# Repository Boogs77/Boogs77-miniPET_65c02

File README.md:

# Boogs77-miniPET: 65C02-Based Retro Computer

The **Boogs77-miniPET** is a compact, high-performance 8-bit computer inspired by the iconic Commodore PET aesthetics. Built around the **W65C02S** processor, this project utilizes the modular architecture of the [BO6502 System](https://github.com/Boogs77/BO6502_65C02-based_modular_computer) and integrates it into a custom-designed, 3D-printed enclosure.

---

## 🧠 System Architecture & Modules

The internal logic of the miniPET is derived directly from the modular boards of the BO6502 project. Each core component follows the same electrical and logical specifications:

### ⚙️ Core Processing Unit (CPU, RAM, ROM)
The system's "brain" and memory management are based on the high-reliability design of the BO6502:
* **CPU:** Western Design Center **W65C02S**, allowing for modern high-speed operation while maintaining full 6502 compatibility. Reference: [BO6502 CPU](https://github.com/Boogs77/BO6502_65C02-based_modular_computer/tree/main/BO6502%20CPU).
* **Clock:** System operates with a stable **1MHz** clock frequency. Reference: [BO6502 CPU](https://github.com/Boogs77/BO6502_65C02-based_modular_computer/tree/main/BO6502%20CPU).

### 🗺️ Memory Map
The memory layout is organized to ensure compatibility with the system firmware and modular hardware:
* **RAM (32KB):** Mapped from **$0000** to **$7FFF**. Reference: [BO6502 RAM](https://github.com/Boogs77/BO6502_65C02-based_modular_computer/tree/main/BO6502%20RAM).
* **ROM (32KB):** Mapped from **$8000** to **$FFFF**. Reference: [BO6502 ROM](https://github.com/Boogs77/BO6502_65C02-based_modular_computer/tree/main/BO6502%20ROM).

### 📟 Display Interface (BIGLCD)
The visual output is handled by the **BIGLCD** module. 
* **Addressing:** The module is mapped and accessible at memory address **$D19X**.
* **Reference:** [BO6502 BIGLCD](https://github.com/Boogs77/BO6502_65C02-based_modular_computer/tree/main/BO6502%20BIGLCD).

### ⌨️ Keyboard Input
Input is managed via a dedicated matrix keyboard interface.
* **Addressing:** The keyboard is mapped and accessible at memory address **$D18X**.
* **Reference:** [BO6502 KeyBoard Module](https://github.com/Boogs77/BO6502_65C02-based_modular_computer/tree/main/BO6502%20KEYb).

### 🔌 Serial Communication
Asynchronous communication is provided for external terminal access.
* **Addressing:** Accessible at the **$CXXX** memory range.
* **Reference:** [BO6502 Serial Module](https://github.com/Boogs77/BO6502_65C02-based_modular_computer/tree/main/BO6502%20SERIAL).

---

## 💻 Software & Firmware

The Boogs77-miniPET features a classic software environment for 6502 enthusiasts:
* **System Monitor:** The computer implements the legendary **Wozmon** monitor, providing a low-level interface for memory inspection and machine code execution.
* **Microsoft BASIC:** The firmware includes **MS BASIC**, allowing for high-level programming.
* **Execution:** BASIC can be launched directly from the monitor by executing from location **$8000**.

---

## 🏗️ Enclosure & 3D Design

One of the most distinctive features of this project is its custom case, modified using **Autodesk Fusion 360** from the original design at [commodorepetmini.com](https://commodorepetmini.com/). The case was printed on an **Anycubic Kobra S1**.

---

## 📋 Bill of Materials (BOM)

| Component | Description | Quantity |
| :--- | :--- | :--- |
| **W65C02S** | CMOS 8-bit Microprocessor | 1 |
| **AS6C62256** | 32K x 8 Static RAM | 1 |
| **AT28C256** | 32K x 8 EEPROM | 1 |
| **W65C22 (VIA)** | Versatile Interface Adapter | 2 |
| **NE555** | Precision Timer (Reset Circuit) | 1 |
| **BIGLCD** | High Contrast LCD Module | 1 |

👉 **[View Full BOM for Components](https://github.com/Boogs77/Boogs77-miniPET_65c02/blob/main/export/miniPET_bom.md)**

---

## 🔗 Useful Links & Resources

To replicate this build, you can refer to the following hardware files:

* **Eagle Design Files:** [Project PCB Schematics & Layouts](https://github.com/Boogs77/Boogs77-miniPET_65c02/tree/main/eagle)
* **CPU Module:** [BO6502 CPU Reference](https://github.com/Boogs77/BO6502_65C02-based_modular_computer/tree/main/BO6502%20CPU)
* **ROM Module:** [BO6502 ROM Reference](https://github.com/Boogs77/BO6502_65C02-based_modular_computer/tree/main/BO6502%20ROM)
* **RAM Module:** [BO6502 RAM Reference](https://github.com/Boogs77/BO6502_65C02-based_modular_computer/tree/main/BO6502%20RAM)
* **Serial Module:** [BO6502 Serial Reference](https://github.com/Boogs77/BO6502_65C02-based_modular_computer/tree/main/BO6502%20SERIAL)
* **Keyboard Module:** [BO6502 KeyBoard Reference](https://github.com/Boogs77/BO6502_65C02-based_modular_computer/tree/main/BO6502%20KEYb)
* **Display Module:** [BO6502 BIGLCD Reference](https://github.com/Boogs77/BO6502_65C02-based_modular_computer/tree/main/BO6502%20BIGLCD)

---

## 🖼️ Project Gallery

Internal assembly and detailed realization stages:

---
*Created by Boogs77 - 2026*

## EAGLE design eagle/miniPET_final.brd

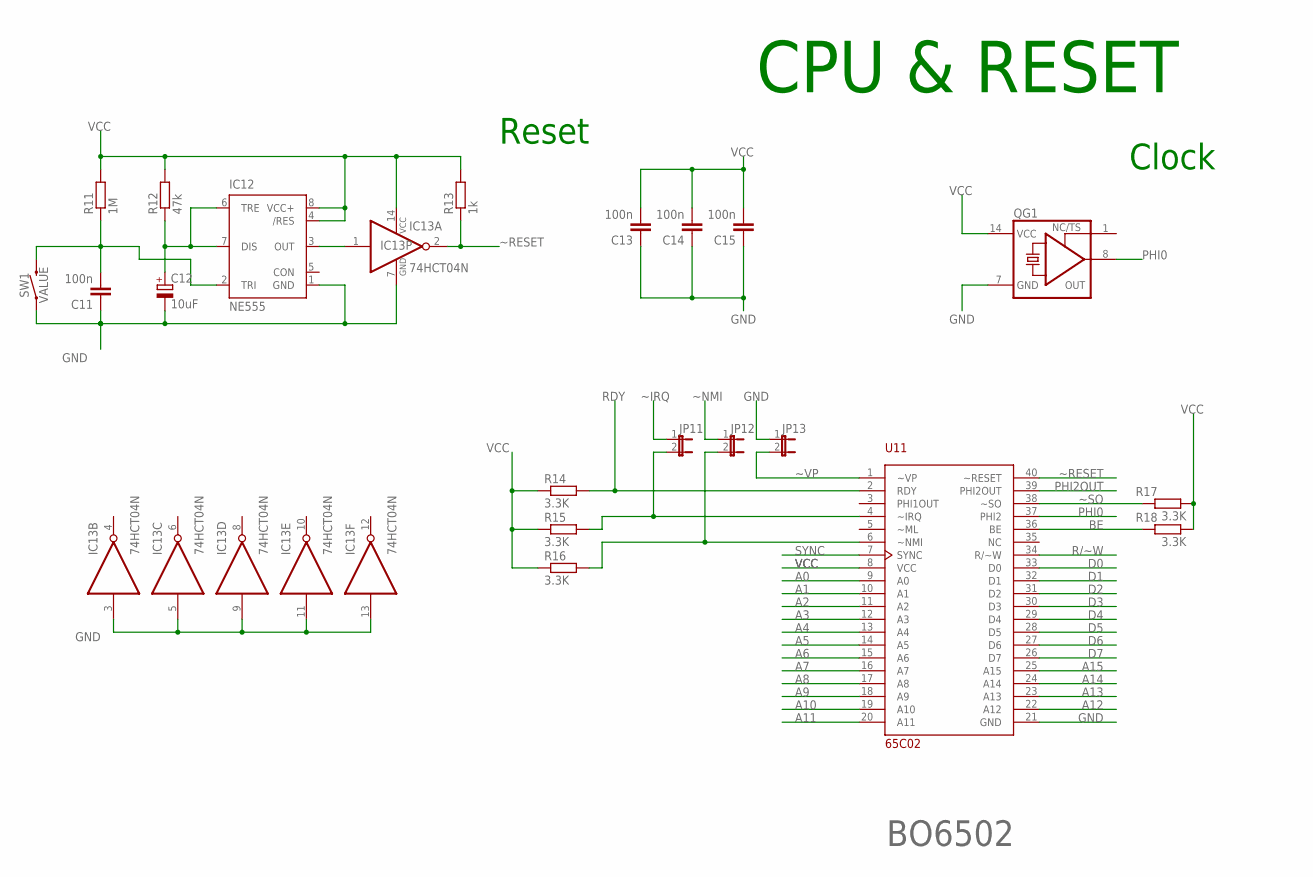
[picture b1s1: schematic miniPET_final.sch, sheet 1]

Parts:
C11, C13, C14, C15: 100n; C025-025X050
C12: 10uF; B45181A
IC12: NE555; DIL-08
IC13: 74HCT04N; DIL14
JP11, JP12, JP13: JP1E; JP1
QG1: XO-14; DIL14S
R11: 1M; 0207/10
R12: 47k; 0207/10
R13: 1k; 0207/10
R14, R15, R16, R17, R18: 3.3K; 0207/10
SW1: MOMENTARY-SWITCH-SPST-PTH-RIGHT-ANGLE-8-020; TACTILE_SWITCH_PTH_RA_8-020
U11: 65C02; DIL40

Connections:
A0: U11.9 (A0); also elsewhere on the board
A1: U11.10 (A1); also elsewhere on the board
A2: U11.11 (A2); also elsewhere on the board
A3: U11.12 (A3); also elsewhere on the board
A4: U11.13 (A4); also elsewhere on the board
A5: U11.14 (A5); also elsewhere on the board
A6: U11.15 (A6); also elsewhere on the board
A7: U11.16 (A7); also elsewhere on the board
A8: U11.17 (A8); also elsewhere on the board
A9: U11.18 (A9); also elsewhere on the board
A10: U11.19 (A10); also elsewhere on the board
A11: U11.20 (A11); also elsewhere on the board
A12: U11.22 (A12); also elsewhere on the board
A13: U11.23 (A13); also elsewhere on the board
A14: U11.24 (A14); also elsewhere on the board
A15: U11.25 (A15); also elsewhere on the board
BE: R18.1, U11.36 (BE)
D0: U11.33 (D0); also elsewhere on the board
D1: U11.32 (D1); also elsewhere on the board
D2: U11.31 (D2); also elsewhere on the board
D3: U11.30 (D3); also elsewhere on the board
D4: U11.29 (D4); also elsewhere on the board
D5: U11.28 (D5); also elsewhere on the board
D6: U11.27 (D6); also elsewhere on the board
D7: U11.26 (D7); also elsewhere on the board
GND: C11.1, C12.-, C13.1, C14.1, C15.1, IC12.1 (GND), IC13.3 (I), IC13.5 (I), IC13.7 (GND), IC13.9 (I), IC13.11 (I), IC13.13 (I), JP13.1, QG1.7 (GND), SW1.1, U11.21 (GND); also elsewhere on the board
unnamed: JP11.2, R15.2, U11.4 (~IRQ)
unnamed: JP12.2, R16.2, U11.6 (~NMI)
unnamed: C12.+, IC12.6 (TRE), IC12.7 (DIS), R12.1
unnamed: C11.2, IC12.2 (TRI), R11.1, SW1.2
unnamed: IC12.3 (OUT), IC13.1 (I)
PHI0: QG1.8 (OUT), U11.37 (PHI2); also elsewhere on the board
PHI2OUT: U11.39 (PHI2OUT)
R/~W: U11.34 (R/~W); also elsewhere on the board
RDY: R14.2, U11.2 (RDY)
SYNC: U11.7 (SYNC)
VCC: C13.2, C14.2, C15.2, IC12.4 (/RES), IC12.8 (VCC+), IC13.14 (VCC), QG1.14 (VCC), R11.2, R12.2, R13.2, R14.1, R15.1, R16.1, R17.2, R18.2, U11.8 (VCC); also elsewhere on the board
~IRQ: JP11.1; also elsewhere on the board
~NMI: JP12.1
~RESET: IC13.2 (O), R13.1, U11.40 (~RESET); also elsewhere on the board
~SO: R17.1, U11.38 (~SO)
~VP: JP13.2, U11.1 (~VP)

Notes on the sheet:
BO6502
CPU & RESET
Clock
Reset

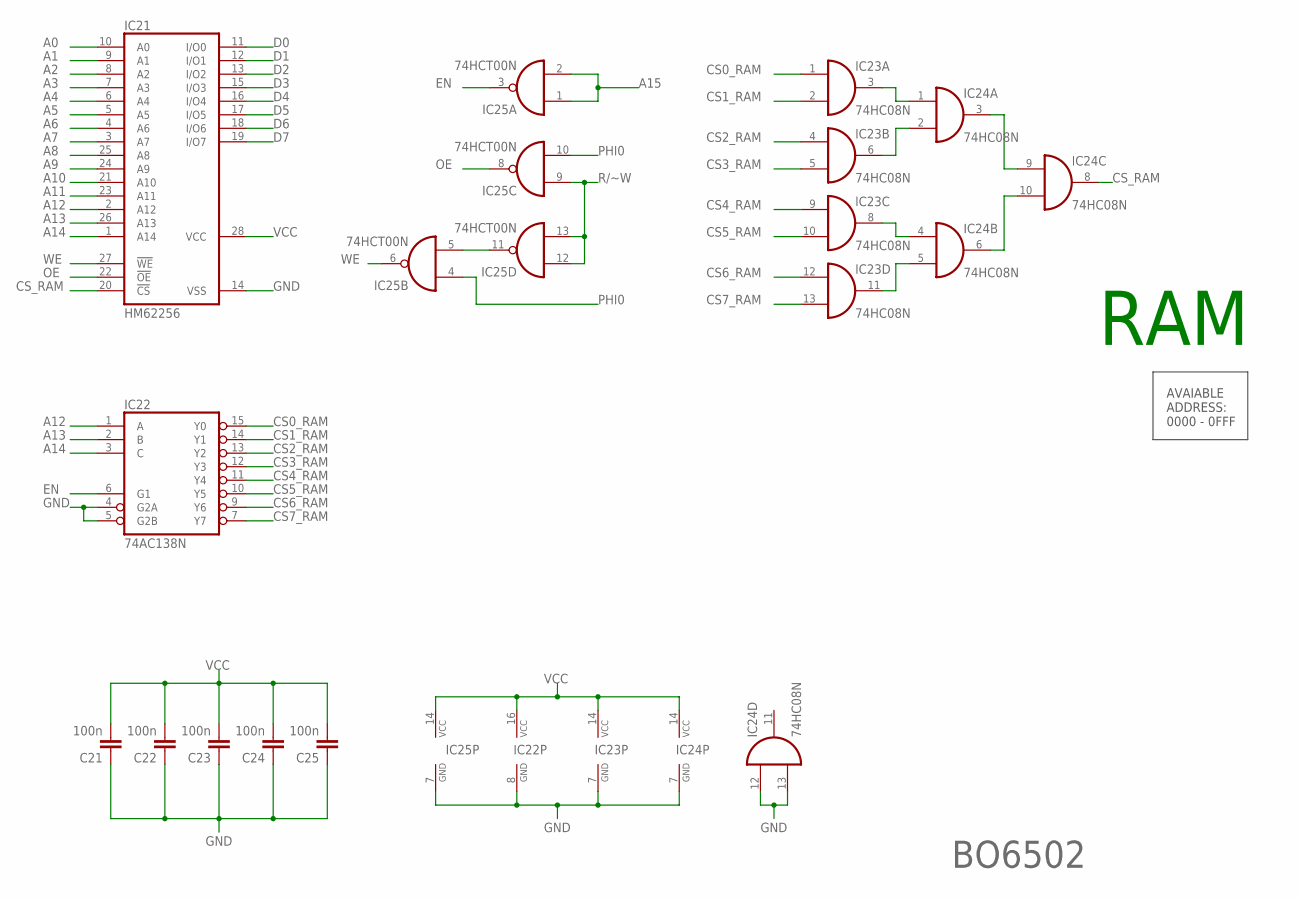
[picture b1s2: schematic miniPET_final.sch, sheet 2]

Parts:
C21, C22, C23, C24, C25: 100n; C025-025X050
IC21: HM62256; DIL28-6
IC22: 74AC138N; DIL16
IC23, IC24: 74HC08N; DIL14
IC25: 74HCT00N; DIL14

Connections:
A0: IC21.10 (A0); also elsewhere on the board
A1: IC21.9 (A1); also elsewhere on the board
A2: IC21.8 (A2); also elsewhere on the board
A3: IC21.7 (A3); also elsewhere on the board
A4: IC21.6 (A4); also elsewhere on the board
A5: IC21.5 (A5); also elsewhere on the board
A6: IC21.4 (A6); also elsewhere on the board
A7: IC21.3 (A7); also elsewhere on the board
A8: IC21.25 (A8); also elsewhere on the board
A9: IC21.24 (A9); also elsewhere on the board
A10: IC21.21 (A10); also elsewhere on the board
A11: IC21.23 (A11); also elsewhere on the board
A12: IC21.2 (A12), IC22.1 (A); also elsewhere on the board
A13: IC21.26 (A13), IC22.2 (B); also elsewhere on the board
A14: IC21.1 (A14), IC22.3 (C); also elsewhere on the board
A15: IC25.1 (I0), IC25.2 (I1); also elsewhere on the board
CS0_RAM: IC22.15 (Y0), IC23.1 (I0)
CS1_RAM: IC22.14 (Y1), IC23.2 (I1)
CS2_RAM: IC22.13 (Y2), IC23.4 (I0)
CS3_RAM: IC22.12 (Y3), IC23.5 (I1)
CS4_RAM: IC22.11 (Y4), IC23.9 (I0)
CS5_RAM: IC22.10 (Y5), IC23.10 (I1)
CS6_RAM: IC22.9 (Y6), IC23.12 (I0)
CS7_RAM: IC22.7 (Y7), IC23.13 (I1)
CS_RAM: IC21.20 (!CS), IC24.8 (O)
D0: IC21.11 (I/O0); also elsewhere on the board
D1: IC21.12 (I/O1); also elsewhere on the board
D2: IC21.13 (I/O2); also elsewhere on the board
D3: IC21.15 (I/O3); also elsewhere on the board
D4: IC21.16 (I/O4); also elsewhere on the board
D5: IC21.17 (I/O5); also elsewhere on the board
D6: IC21.18 (I/O6); also elsewhere on the board
D7: IC21.19 (I/O7); also elsewhere on the board
EN: IC22.6 (G1), IC25.3 (O)
GND: C21.1, C22.1, C23.1, C24.1, C25.1, IC21.14 (VSS), IC22.4 (G2A), IC22.5 (G2B), IC22.8 (GND), IC23.7 (GND), IC24.7 (GND), IC24.12 (I0), IC24.13 (I1), IC25.7 (GND); also elsewhere on the board
unnamed: IC25.5 (I1), IC25.11 (O)
unnamed: IC23.3 (O), IC24.1 (I0)
unnamed: IC23.6 (O), IC24.2 (I1)
unnamed: IC23.8 (O), IC24.4 (I0)
unnamed: IC23.11 (O), IC24.5 (I1)
unnamed: IC24.3 (O), IC24.9 (I0)
unnamed: IC24.6 (O), IC24.10 (I1)
OE: IC21.22 (!OE), IC25.8 (O)
PHI0: IC25.4 (I0), IC25.10 (I1); also elsewhere on the board
R/~W: IC25.9 (I0), IC25.12 (I0), IC25.13 (I1); also elsewhere on the board
VCC: C21.2, C22.2, C23.2, C24.2, C25.2, IC21.28 (VCC), IC22.16 (VCC), IC23.14 (VCC), IC24.14 (VCC), IC25.14 (VCC); also elsewhere on the board
WE: IC21.27 (!WE), IC25.6 (O)

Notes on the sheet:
RAM
BO6502
AVAIABLE ADDRESS: 0000 - 0FFF

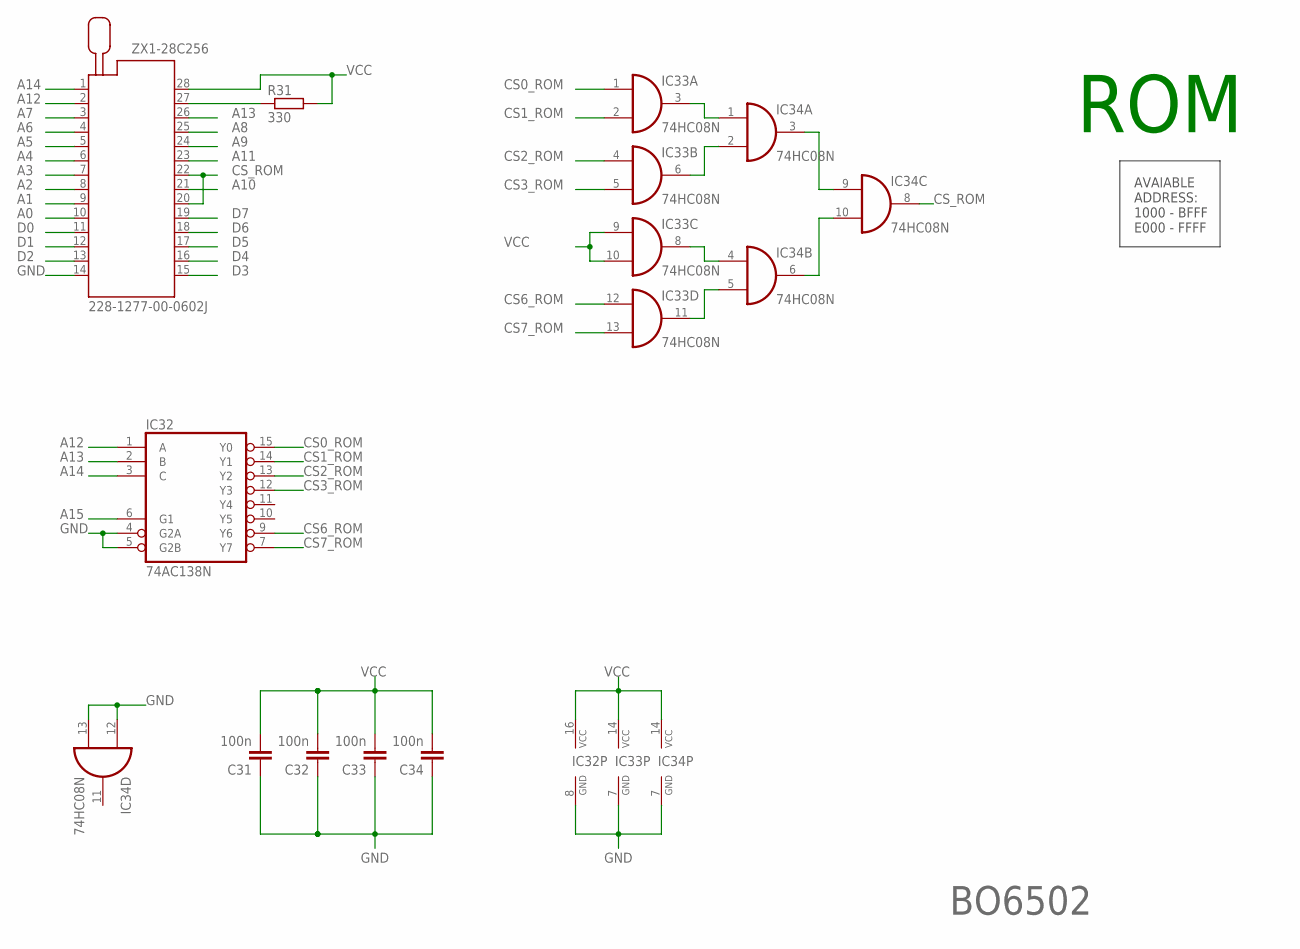
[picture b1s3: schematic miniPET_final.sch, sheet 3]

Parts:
C31, C32, C33, C34: 100n; C025-025X050
IC32: 74AC138N; DIL16
IC33, IC34: 74HC08N; DIL14
R31: 330; 0207/10
ZX1-28C256: 228-1277-00-0602J

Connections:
A0: ZX1-28C256.10; also elsewhere on the board
A1: ZX1-28C256.9; also elsewhere on the board
A2: ZX1-28C256.8; also elsewhere on the board
A3: ZX1-28C256.7; also elsewhere on the board
A4: ZX1-28C256.6; also elsewhere on the board
A5: ZX1-28C256.5; also elsewhere on the board
A6: ZX1-28C256.4; also elsewhere on the board
A7: ZX1-28C256.3; also elsewhere on the board
A8: ZX1-28C256.25; also elsewhere on the board
A9: ZX1-28C256.24; also elsewhere on the board
A10: ZX1-28C256.21; also elsewhere on the board
A11: ZX1-28C256.23; also elsewhere on the board
A12: IC32.1 (A), ZX1-28C256.2; also elsewhere on the board
A13: IC32.2 (B), ZX1-28C256.26; also elsewhere on the board
A14: IC32.3 (C), ZX1-28C256.1; also elsewhere on the board
A15: IC32.6 (G1); also elsewhere on the board
CS0_ROM: IC32.15 (Y0), IC33.1 (I0)
CS1_ROM: IC32.14 (Y1), IC33.2 (I1)
CS2_ROM: IC32.13 (Y2), IC33.4 (I0)
CS3_ROM: IC32.12 (Y3), IC33.5 (I1)
CS6_ROM: IC32.9 (Y6), IC33.12 (I0)
CS7_ROM: IC32.7 (Y7), IC33.13 (I1)
CS_ROM: IC34.8 (O), ZX1-28C256.20, ZX1-28C256.22
D0: ZX1-28C256.11; also elsewhere on the board
D1: ZX1-28C256.12; also elsewhere on the board
D2: ZX1-28C256.13; also elsewhere on the board
D3: ZX1-28C256.15; also elsewhere on the board
D4: ZX1-28C256.16; also elsewhere on the board
D5: ZX1-28C256.17; also elsewhere on the board
D6: ZX1-28C256.18; also elsewhere on the board
D7: ZX1-28C256.19; also elsewhere on the board
GND: C31.1, C32.1, C33.1, C34.1, IC32.4 (G2A), IC32.5 (G2B), IC32.8 (GND), IC33.7 (GND), IC34.7 (GND), IC34.12 (I0), IC34.13 (I1), ZX1-28C256.14; also elsewhere on the board
unnamed: R31.1, ZX1-28C256.27
unnamed: IC33.3 (O), IC34.1 (I0)
unnamed: IC33.6 (O), IC34.2 (I1)
unnamed: IC33.8 (O), IC34.4 (I0)
unnamed: IC33.11 (O), IC34.5 (I1)
unnamed: IC34.3 (O), IC34.9 (I0)
unnamed: IC34.6 (O), IC34.10 (I1)
VCC: C31.2, C32.2, C33.2, C34.2, IC32.16 (VCC), IC33.9 (I0), IC33.10 (I1), IC33.14 (VCC), IC34.14 (VCC), R31.2, ZX1-28C256.28; also elsewhere on the board

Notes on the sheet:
ROM
BO6502
AVAIABLE ADDRESS: 1000 - BFFF E000 - FFFF

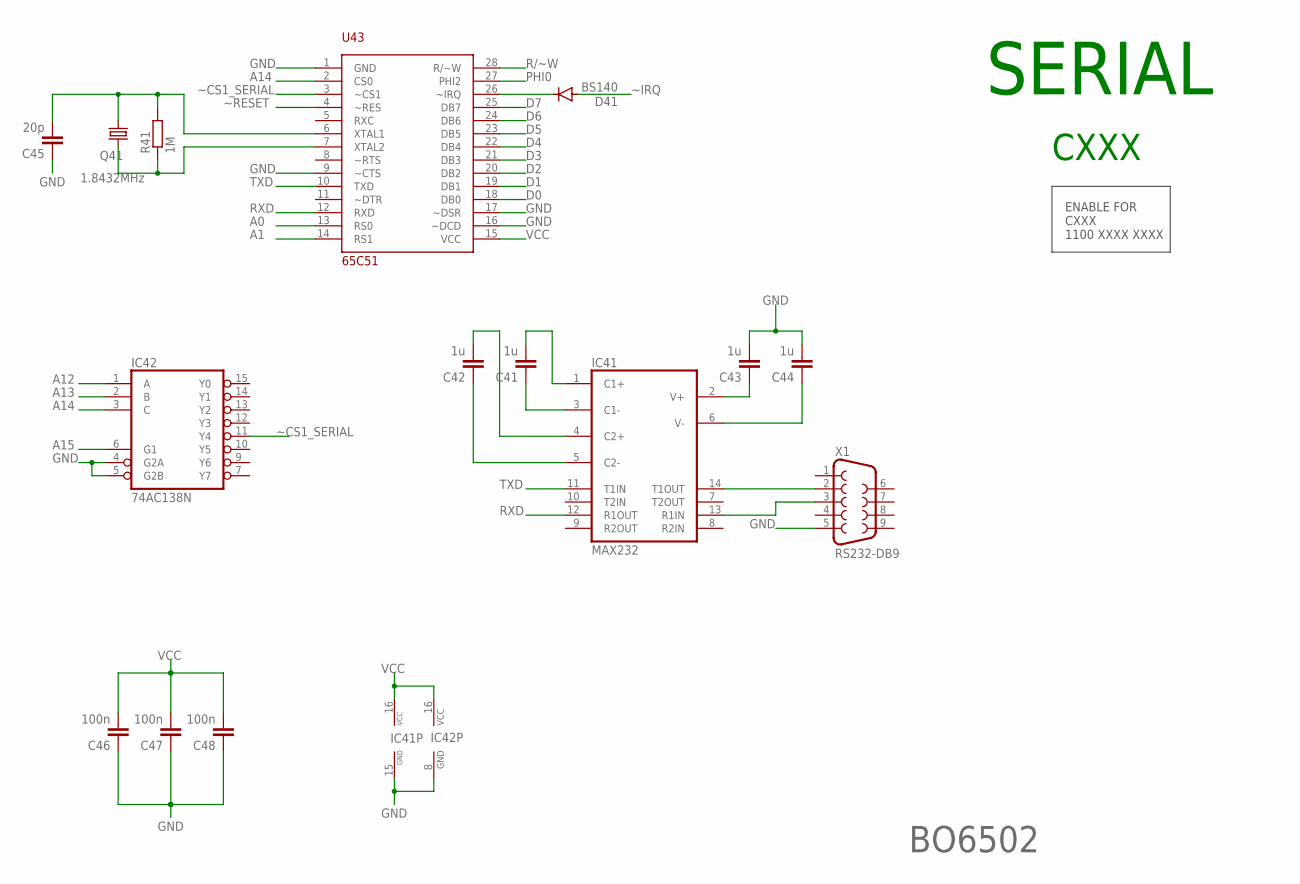
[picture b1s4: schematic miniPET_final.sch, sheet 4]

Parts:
C41, C42, C43, C44: 1u; C050-025X075
C45: 20p; C025-025X050
C46, C47, C48: 100n; C025-025X050
D41: BS140; DO41-10
IC41: MAX232; DIL16
IC42: 74AC138N; DIL16
Q41: 1.8432MHz; HC49/S
R41: 1M; 0207/10
U43: 65C51; DIL28
X1: RS232-DB9; F09HP

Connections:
A0: U43.13 (RS0); also elsewhere on the board
A1: U43.14 (RS1); also elsewhere on the board
A12: IC42.1 (A); also elsewhere on the board
A13: IC42.2 (B); also elsewhere on the board
A14: IC42.3 (C), U43.2 (CS0); also elsewhere on the board
A15: IC42.6 (G1); also elsewhere on the board
D0: U43.18 (DB0); also elsewhere on the board
D1: U43.19 (DB1); also elsewhere on the board
D2: U43.20 (DB2); also elsewhere on the board
D3: U43.21 (DB3); also elsewhere on the board
D4: U43.22 (DB4); also elsewhere on the board
D5: U43.23 (DB5); also elsewhere on the board
D6: U43.24 (DB6); also elsewhere on the board
D7: U43.25 (DB7); also elsewhere on the board
GND: C43.2, C44.2, C45.1, C46.1, C47.1, C48.1, IC41.15 (GND), IC42.4 (G2A), IC42.5 (G2B), IC42.8 (GND), U43.1 (GND), U43.9 (~CTS), U43.16 (~DCD), U43.17 (~DSR), X1.5; also elsewhere on the board
unnamed: D41.C, U43.26 (~IRQ)
unnamed: C41.2, IC41.1 (C1+)
unnamed: C41.1, IC41.3 (C1-)
unnamed: C42.1, IC41.5 (C2-)
unnamed: IC41.14 (T1OUT), X1.2
unnamed: IC41.13 (R1IN), X1.3
unnamed: C43.1, IC41.2 (V+)
unnamed: C44.1, IC41.6 (V-)
unnamed: C42.2, IC41.4 (C2+)
unnamed: C45.2, Q41.2, R41.2, U43.6 (XTAL1)
unnamed: Q41.1, R41.1, U43.7 (XTAL2)
PHI0: U43.27 (PHI2); also elsewhere on the board
R/~W: U43.28 (R/~W); also elsewhere on the board
RXD: IC41.12 (R1OUT), U43.12 (RXD)
TXD: IC41.11 (T1IN), U43.10 (TXD)
VCC: C46.2, C47.2, C48.2, IC41.16 (VCC), IC42.16 (VCC), U43.15 (VCC); also elsewhere on the board
~CS1_SERIAL: IC42.11 (Y4), U43.3 (~CS1)
~IRQ: D41.A; also elsewhere on the board
~RESET: U43.4 (~RES); also elsewhere on the board

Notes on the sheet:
SERIAL
CXXX
BO6502
ENABLE FOR CXXX 1100 XXXX XXXX

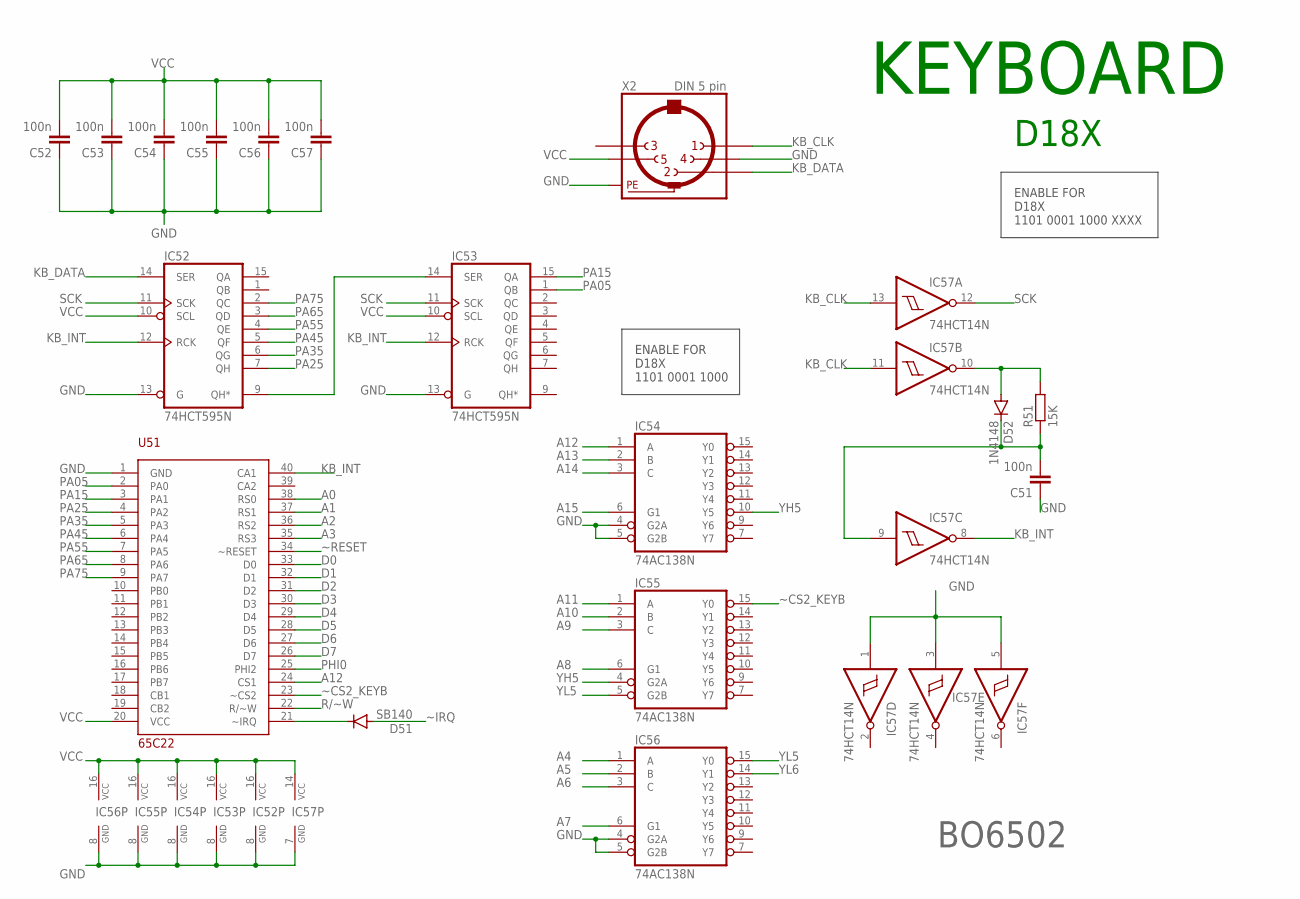
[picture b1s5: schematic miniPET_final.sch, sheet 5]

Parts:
C51, C52, C53, C54, C55, C56, C57: 100n; C025-025X050
D51: SB140; DO41-10
D52: 1N4148; DO35-7
IC52, IC53: 74HCT595N; DIL16
IC54, IC55, IC56: 74AC138N; DIL16
IC57: 74HCT14N; DIL14
R51: 15K; 0207/10
U51: 65C22; DIL40
X2: DIN 5 pin; MAB5SH

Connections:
A0: U51.38 (RS0); also elsewhere on the board
A1: U51.37 (RS1); also elsewhere on the board
A2: U51.36 (RS2); also elsewhere on the board
A3: U51.35 (RS3); also elsewhere on the board
A4: IC56.1 (A); also elsewhere on the board
A5: IC56.2 (B); also elsewhere on the board
A6: IC56.3 (C); also elsewhere on the board
A7: IC56.6 (G1); also elsewhere on the board
A8: IC55.6 (G1); also elsewhere on the board
A9: IC55.3 (C); also elsewhere on the board
A10: IC55.2 (B); also elsewhere on the board
A11: IC55.1 (A); also elsewhere on the board
A12: IC54.1 (A), U51.24 (CS1); also elsewhere on the board
A13: IC54.2 (B); also elsewhere on the board
A14: IC54.3 (C); also elsewhere on the board
A15: IC54.6 (G1); also elsewhere on the board
D0: U51.33 (D0); also elsewhere on the board
D1: U51.32 (D1); also elsewhere on the board
D2: U51.31 (D2); also elsewhere on the board
D3: U51.30 (D3); also elsewhere on the board
D4: U51.29 (D4); also elsewhere on the board
D5: U51.28 (D5); also elsewhere on the board
D6: U51.27 (D6); also elsewhere on the board
D7: U51.26 (D7); also elsewhere on the board
GND: C51.1, C52.1, C53.1, C54.1, C55.1, C56.1, C57.1, IC52.8 (GND), IC52.13 (G), IC53.8 (GND), IC53.13 (G), IC54.4 (G2A), IC54.5 (G2B), IC54.8 (GND), IC55.8 (GND), IC56.4 (G2A), IC56.5 (G2B), IC56.8 (GND), IC57.1 (I), IC57.3 (I), IC57.5 (I), IC57.7 (GND), U51.1 (GND), X2.4, X2.PE, X2.PE@ (PE); also elsewhere on the board
KB_CLK: IC57.11 (I), IC57.13 (I), X2.1
KB_DATA: IC52.14 (SER), X2.2
KB_INT: IC52.12 (RCK), IC53.12 (RCK), IC57.8 (O), U51.40 (CA1)
unnamed: D51.C, U51.21 (~IRQ)
unnamed: IC52.9 (QH*), IC53.14 (SER)
unnamed: D52.A, IC57.10 (O), R51.2
unnamed: C51.2, D52.C, IC57.9 (I), R51.1
PA05: IC53.1 (QB), U51.2 (PA0)
PA15: IC53.15 (QA), U51.3 (PA1)
PA25: IC52.7 (QH), U51.4 (PA2)
PA35: IC52.6 (QG), U51.5 (PA3)
PA45: IC52.5 (QF), U51.6 (PA4)
PA55: IC52.4 (QE), U51.7 (PA5)
PA65: IC52.3 (QD), U51.8 (PA6)
PA75: IC52.2 (QC), U51.9 (PA7)
PHI0: U51.25 (PHI2); also elsewhere on the board
R/~W: U51.22 (R/~W); also elsewhere on the board
SCK: IC52.11 (SCK), IC53.11 (SCK), IC57.12 (O)
VCC: C52.2, C53.2, C54.2, C55.2, C56.2, C57.2, IC52.10 (SCL), IC52.16 (VCC), IC53.10 (SCL), IC53.16 (VCC), IC54.16 (VCC), IC55.16 (VCC), IC56.16 (VCC), IC57.14 (VCC), U51.20 (VCC), X2.5; also elsewhere on the board
YH5: IC54.10 (Y5), IC55.4 (G2A); also elsewhere on the board
YL5: IC55.5 (G2B), IC56.15 (Y0)
YL6: IC56.14 (Y1); also elsewhere on the board
~CS2_KEYB: IC55.15 (Y0), U51.23 (~CS2)
~IRQ: D51.A; also elsewhere on the board
~RESET: U51.34 (~RESET); also elsewhere on the board

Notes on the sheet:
KEYBOARD
ENABLE FOR D18X 1101 0001 1000
D18X
BO6502
ENABLE FOR D18X 1101 0001 1000 XXXX

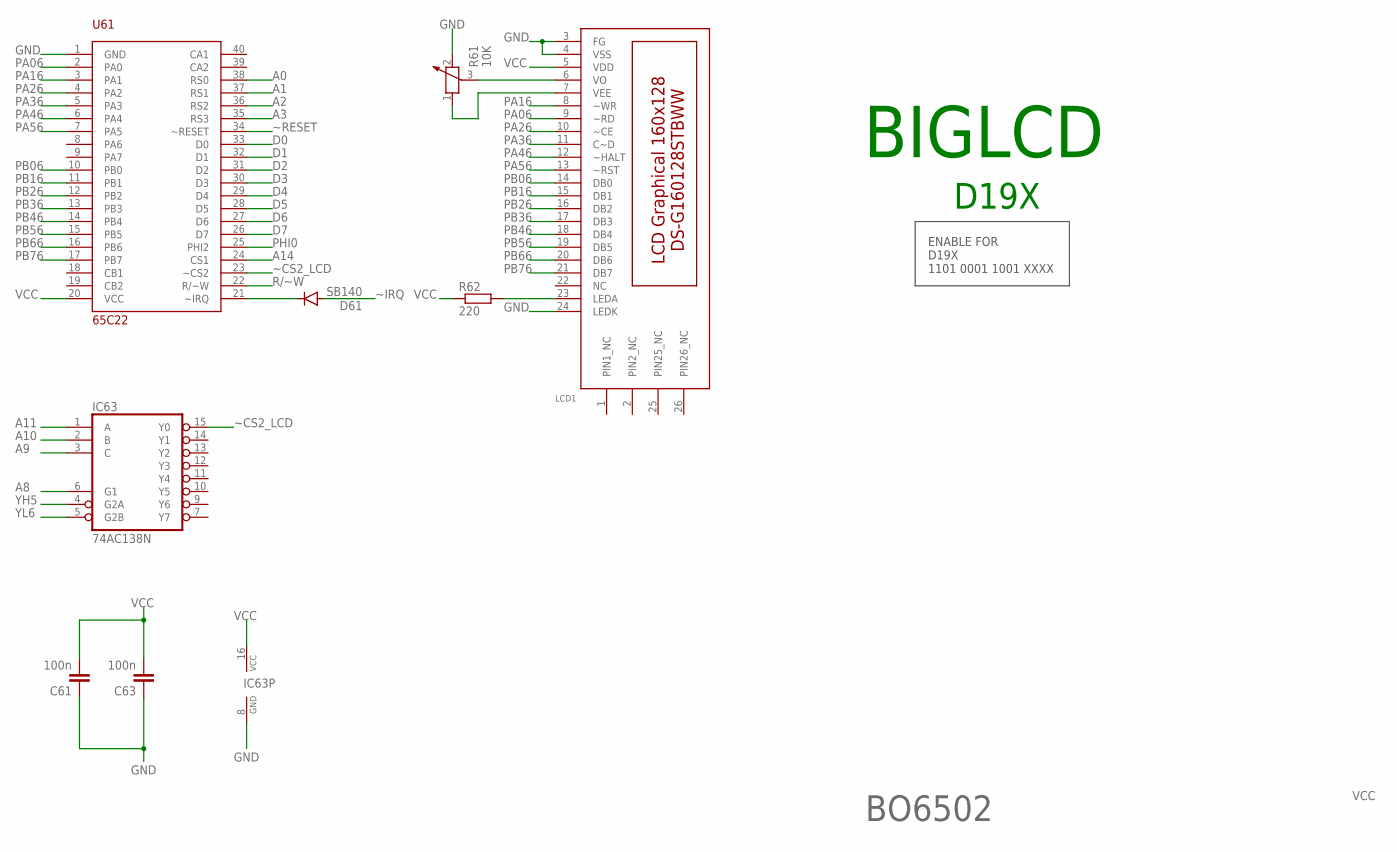
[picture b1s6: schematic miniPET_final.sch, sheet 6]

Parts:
C61, C63: 100n; C025-025X050
D61: SB140; DO41-10
IC63: 74AC138N; DIL16
LCD1: DS-G160128STBWW; PAK100/2500-26
R61: 10K; PT-10
R62: 220; 0207/10
U61: 65C22; DIL40

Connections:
A0: U61.38 (RS0); also elsewhere on the board
A1: U61.37 (RS1); also elsewhere on the board
A2: U61.36 (RS2); also elsewhere on the board
A3: U61.35 (RS3); also elsewhere on the board
A8: IC63.6 (G1); also elsewhere on the board
A9: IC63.3 (C); also elsewhere on the board
A10: IC63.2 (B); also elsewhere on the board
A11: IC63.1 (A); also elsewhere on the board
A14: U61.24 (CS1); also elsewhere on the board
D0: U61.33 (D0); also elsewhere on the board
D1: U61.32 (D1); also elsewhere on the board
D2: U61.31 (D2); also elsewhere on the board
D3: U61.30 (D3); also elsewhere on the board
D4: U61.29 (D4); also elsewhere on the board
D5: U61.28 (D5); also elsewhere on the board
D6: U61.27 (D6); also elsewhere on the board
D7: U61.26 (D7); also elsewhere on the board
GND: C61.1, C63.1, IC63.8 (GND), LCD1.3 (FG), LCD1.4 (VSS), LCD1.24 (LEDK), R61.2, U61.1 (GND); also elsewhere on the board
unnamed: D61.C, U61.21 (~IRQ)
unnamed: LCD1.6 (VO), R61.3
unnamed: LCD1.7 (VEE), R61.1
unnamed: LCD1.23 (LEDA), R62.2
PA06: LCD1.9 (~RD), U61.2 (PA0)
PA16: LCD1.8 (~WR), U61.3 (PA1)
PA26: LCD1.10 (~CE), U61.4 (PA2)
PA36: LCD1.11 (C~D), U61.5 (PA3)
PA46: LCD1.12 (~HALT), U61.6 (PA4)
PA56: LCD1.13 (~RST), U61.7 (PA5)
PB06: LCD1.14 (DB0), U61.10 (PB0)
PB16: LCD1.15 (DB1), U61.11 (PB1)
PB26: LCD1.16 (DB2), U61.12 (PB2)
PB36: LCD1.17 (DB3), U61.13 (PB3)
PB46: LCD1.18 (DB4), U61.14 (PB4)
PB56: LCD1.19 (DB5), U61.15 (PB5)
PB66: LCD1.20 (DB6), U61.16 (PB6)
PB76: LCD1.21 (DB7), U61.17 (PB7)
PHI0: U61.25 (PHI2); also elsewhere on the board
R/~W: U61.22 (R/~W); also elsewhere on the board
VCC: C61.2, C63.2, IC63.16 (VCC), LCD1.5 (VDD), R62.1, U61.20 (VCC); also elsewhere on the board
YH5: IC63.4 (G2A); also elsewhere on the board
YL6: IC63.5 (G2B); also elsewhere on the board
~CS2_LCD: IC63.15 (Y0), U61.23 (~CS2)
~IRQ: D61.A; also elsewhere on the board
~RESET: U61.34 (~RESET); also elsewhere on the board

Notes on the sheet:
BIGLCD
D19X
BO6502
ENABLE FOR D19X 1101 0001 1001 XXXX

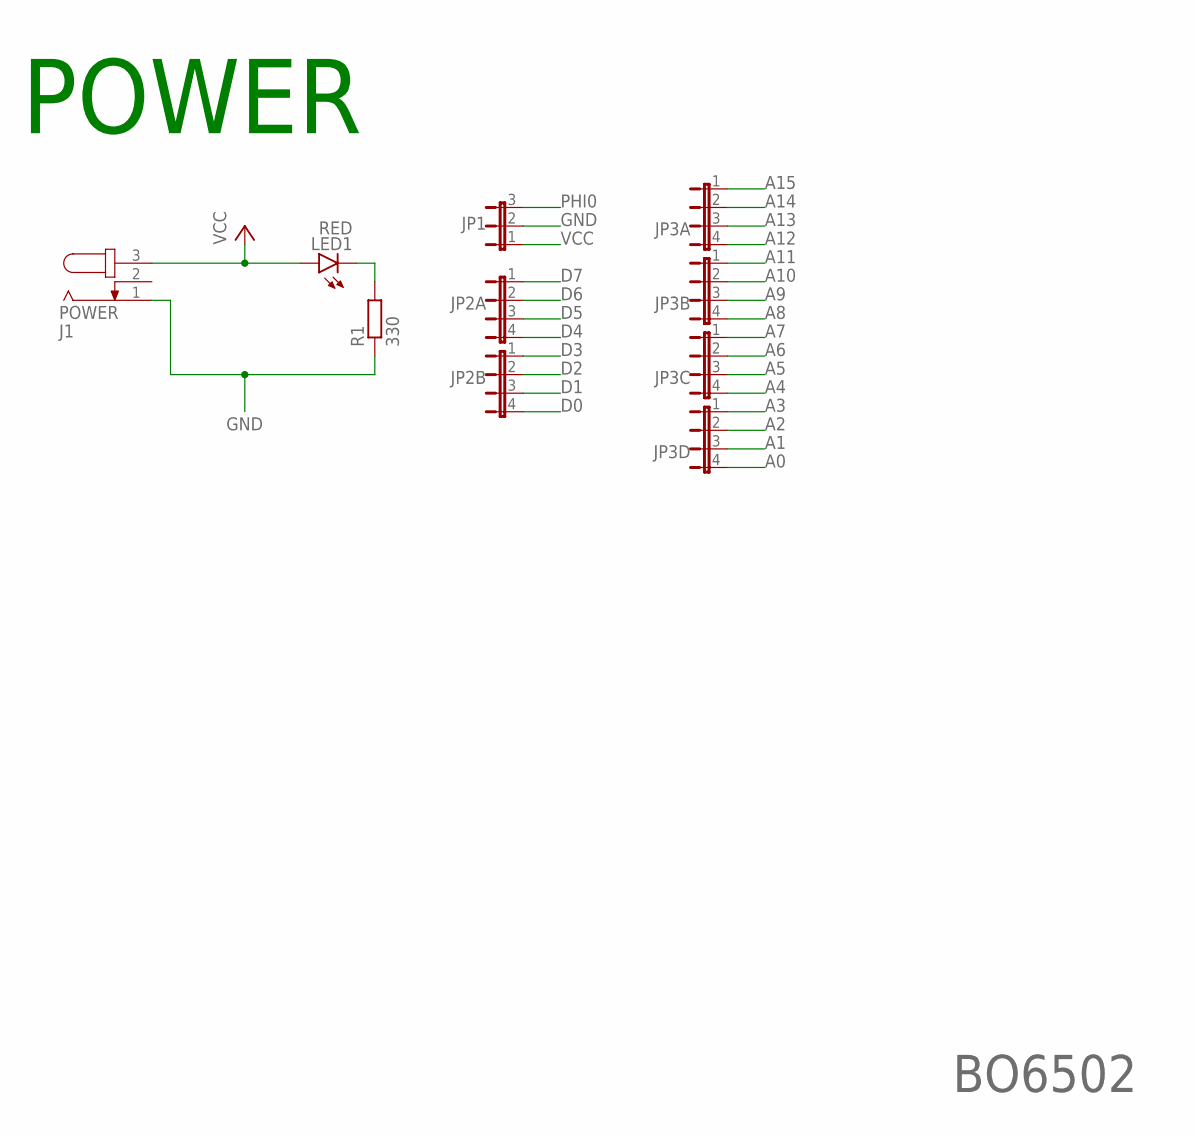
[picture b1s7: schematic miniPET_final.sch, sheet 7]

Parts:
J1: POWER; SPC4078
JP1: JP2E; JP2
JP2A, JP2B, JP3A, JP3B, JP3C, JP3D: JP4E; JP4
LED1: RED; LED5MM
R1: 330; 0207/10

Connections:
A0: JP3D.4; also elsewhere on the board
A1: JP3D.3; also elsewhere on the board
A2: JP3D.2; also elsewhere on the board
A3: JP3D.1; also elsewhere on the board
A4: JP3C.4; also elsewhere on the board
A5: JP3C.3; also elsewhere on the board
A6: JP3C.2; also elsewhere on the board
A7: JP3C.1; also elsewhere on the board
A8: JP3B.4; also elsewhere on the board
A9: JP3B.3; also elsewhere on the board
A10: JP3B.2; also elsewhere on the board
A11: JP3B.1; also elsewhere on the board
A12: JP3A.4; also elsewhere on the board
A13: JP3A.3; also elsewhere on the board
A14: JP3A.2; also elsewhere on the board
A15: JP3A.1; also elsewhere on the board
D0: JP2B.4; also elsewhere on the board
D1: JP2B.3; also elsewhere on the board
D2: JP2B.2; also elsewhere on the board
D3: JP2B.1; also elsewhere on the board
D4: JP2A.4; also elsewhere on the board
D5: JP2A.3; also elsewhere on the board
D6: JP2A.2; also elsewhere on the board
D7: JP2A.1; also elsewhere on the board
GND: J1.1, JP1.2, R1.1; also elsewhere on the board
unnamed: LED1.K (C), R1.2
PHI0: JP1.3; also elsewhere on the board
VCC: J1.3, JP1.1, LED1.A; also elsewhere on the board

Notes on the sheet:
POWER
BO6502

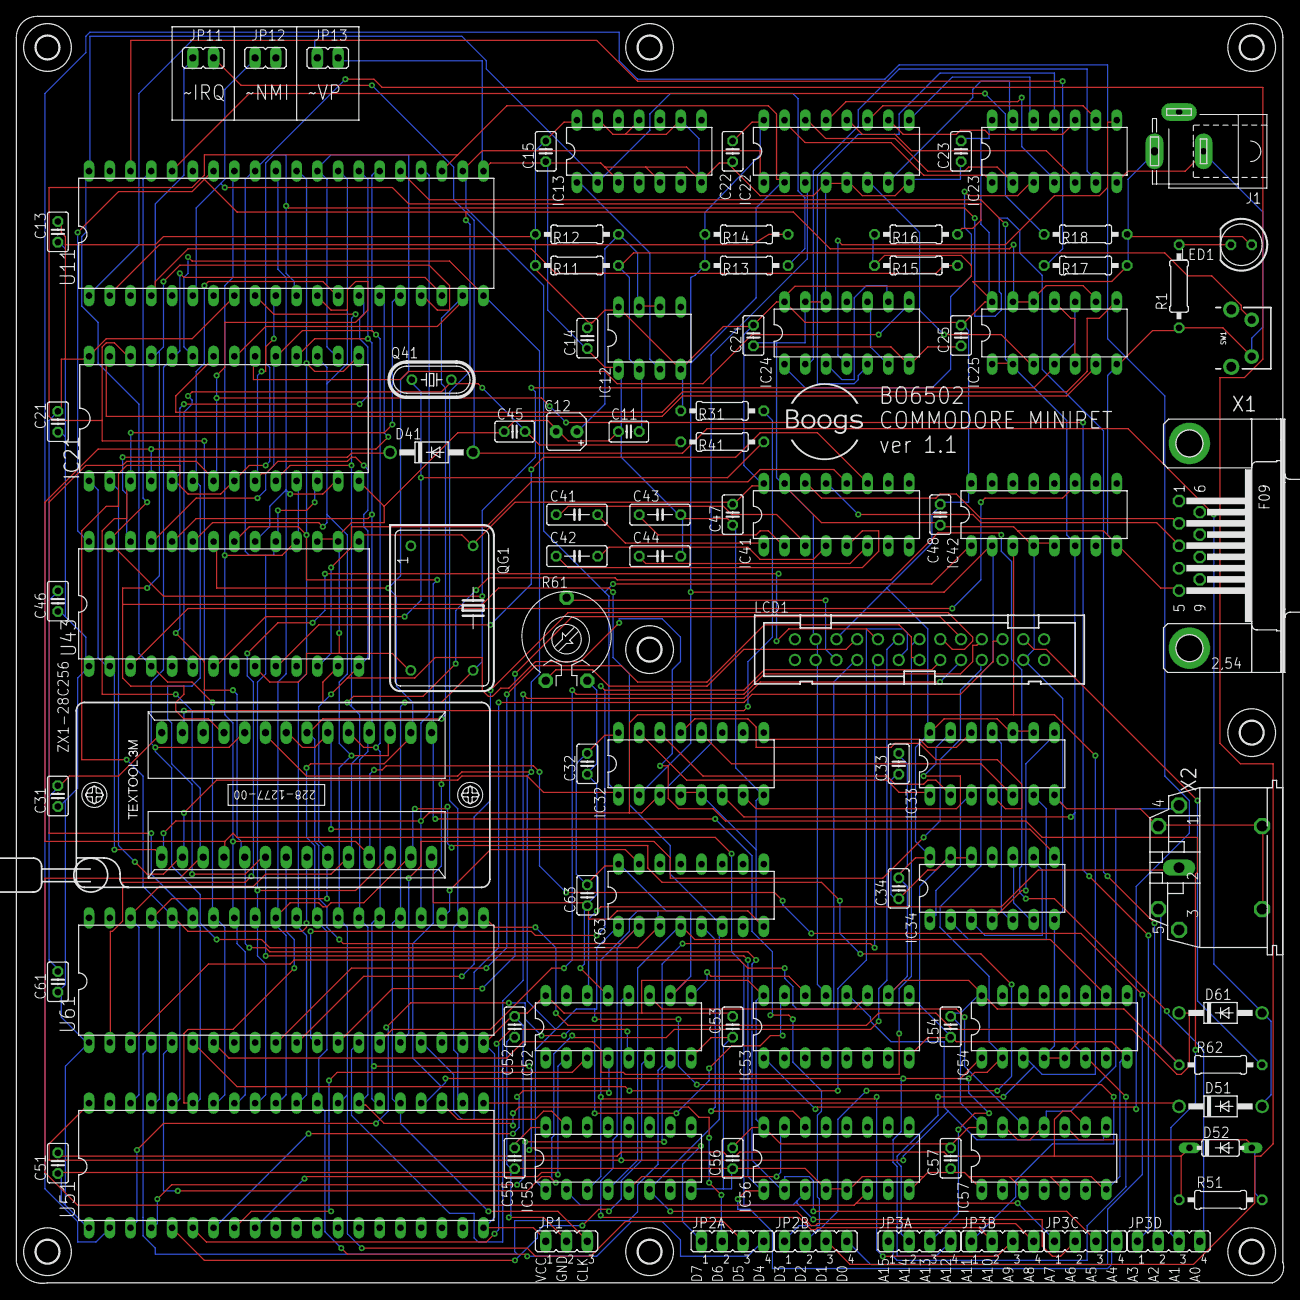
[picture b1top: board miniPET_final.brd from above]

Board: 2 copper layers, 155.0 x 155.0 mm, 99 parts (0 on the bottom side), 126 nets.

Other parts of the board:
U$1, U$2, U$3, U$4, U$5, U$6, U$7, U$8: 2,8

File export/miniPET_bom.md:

# 📑 Bill of Materials (BOM): miniPET 1.0

**Project:** miniPET
**Export Date:** 02/02/2026
**Source File:** `miniPET_final.sch`

---

### 🧠 Integrated Circuits (IC) & Logic
| Qty | Part | Value | Description | Package |
| :--- | :--- | :--- | :--- | :--- |
| 1 | **U11** | 65C02 | 8-bit CMOS CPU | DIL40 |
| 2 | **U51, U61** | 65C22 | VIA (Versatile Interface Adapter) | DIL40 |
| 1 | **U43** | 65C51 | ACIA (Serial Interface) | DIL28 |
| 1 | **IC21** | HM62256 | Static RAM (SRAM) | DIL28-6 |
| 1 | **ZX1-28C256** | 228-1277-00-0602J | Zero Insertion Force (ZIF) Socket | 228-1277-00-0602J |
| 7 | **IC22, IC32, IC42, IC54, IC55, IC56, IC63** | 74AC138N | 3-to-8 Decoder/Demultiplexer | DIL16 |
| 4 | **IC23, IC24, IC33, IC34** | 74HC08N | Quad 2-input AND gate | DIL14 |
| 2 | **IC52, IC53** | 74HCT595N | 8-bit Shift Register with output latch | DIL16 |
| 1 | **IC41** | MAX232 | RS232 Transceiver | DIL16 |
| 1 | **IC12** | NE555 | General purpose bipolar Timer | DIL-08 |
| 1 | **IC13** | 74HCT04N | Hex INVERTER | DIL14 |
| 1 | **IC57** | 74HCT14N | Hex Schmitt Trigger Inverter | DIL14 |
| 1 | **IC25** | 74HCT00N | Quad 2-input NAND gate | DIL14 |

---

### ⚡ Resistors & Potentiometers
| Qty | Part | Value | Description | Package |
| :--- | :--- | :--- | :--- | :--- |
| 5 | **R14, R15, R16, R17, R18** | 3.3K | Standard Resistor | 0207/10 |
| 2 | **R1, R31** | 330 | Standard Resistor | 0207/10 |
| 2 | **R11, R41** | 1M | Standard Resistor | 0207/10 |
| 1 | **R12** | 47k | Standard Resistor | 0207/10 |
| 1 | **R13** | 1k | Standard Resistor | 0207/10 |
| 1 | **R51** | 15K | Standard Resistor | 0207/10 |
| 1 | **R62** | 220 | Standard Resistor | 0207/10 |
| 1 | **R61** | 10K | Potentiometer | PT-10 |

---

### 🔋 Capacitors
| Qty | Part | Value | Description | Package |
| :--- | :--- | :--- | :--- | :--- |
| 22 | **C11, C13-15, C21-25, C31-34, C46-48, C51-57, C61, C63** | 100n | Ceramic Capacitor (Decoupling) | C025-025X050 |
| 4 | **C41, C42, C43, C44** | 1u | Ceramic Capacitor | C050-025X075 |
| 1 | **C12** | 10uF | Polarized Capacitor | B45181A |
| 1 | **C45** | 20p | Ceramic Capacitor (for Crystal) | C025-025X050 |

---

### 💎 Diodes & Crystals
| Qty | Part | Value | Description | Package |
| :--- | :--- | :--- | :--- | :--- |
| 1 | **Q41** | 1.8432MHz | Crystal | HC49/S |
| 1 | **QG1** | - | Crystal Oscillator | DIL14S |
| 3 | **D41, D51, D61** | BS140 / SB140 | Diode (Equiv. 1N4004) | DO41-10 |
| 1 | **D52** | 1N4148 | Fast Signal Diode | DO35-7 |
| 1 | **LED1** | RED | 5mm LED | LED5MM |

---

### 🔌 Connectors, Switches & Display
| Qty | Part | Value | Description | Package |
| :--- | :--- | :--- | :--- | :--- |
| 1 | **LCD1** | DS-G160128STBWW | Graphic LCD | PAK100 |
| 1 | **J1** | POWER | DC Power Jack | SPC4078 |
| 1 | **X1** | RS232-DB9 | SUB-D 9-pin Connector | F09HP |
| 1 | **X2** | DIN 5 pin | Female DIN Connector | MAB5SH |
| 1 | **SW1** | MOMENTARY | Momentary Pushbutton (Reset) | TACTILE_RA |
| 11 | **JP1, JP11-13, JP2A-B, JP3A-D** | - | Jumper Headers | JP1 / JP2 / JP4 |

---

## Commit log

2026-02-03 Add initial content to README.md
2026-02-03 add files
2026-02-03 add pics
2026-02-03 add images
2026-02-03 Rename project in README
    Updated project name from 'Boogs77-miniPET' to 'miniPET'.

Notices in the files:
parts and their libraries:
SparkFun-Switches: Licensing: Creative Commons ShareAlike 4.0 International - https://creativecommons.org/licenses/by-sa/4.0
